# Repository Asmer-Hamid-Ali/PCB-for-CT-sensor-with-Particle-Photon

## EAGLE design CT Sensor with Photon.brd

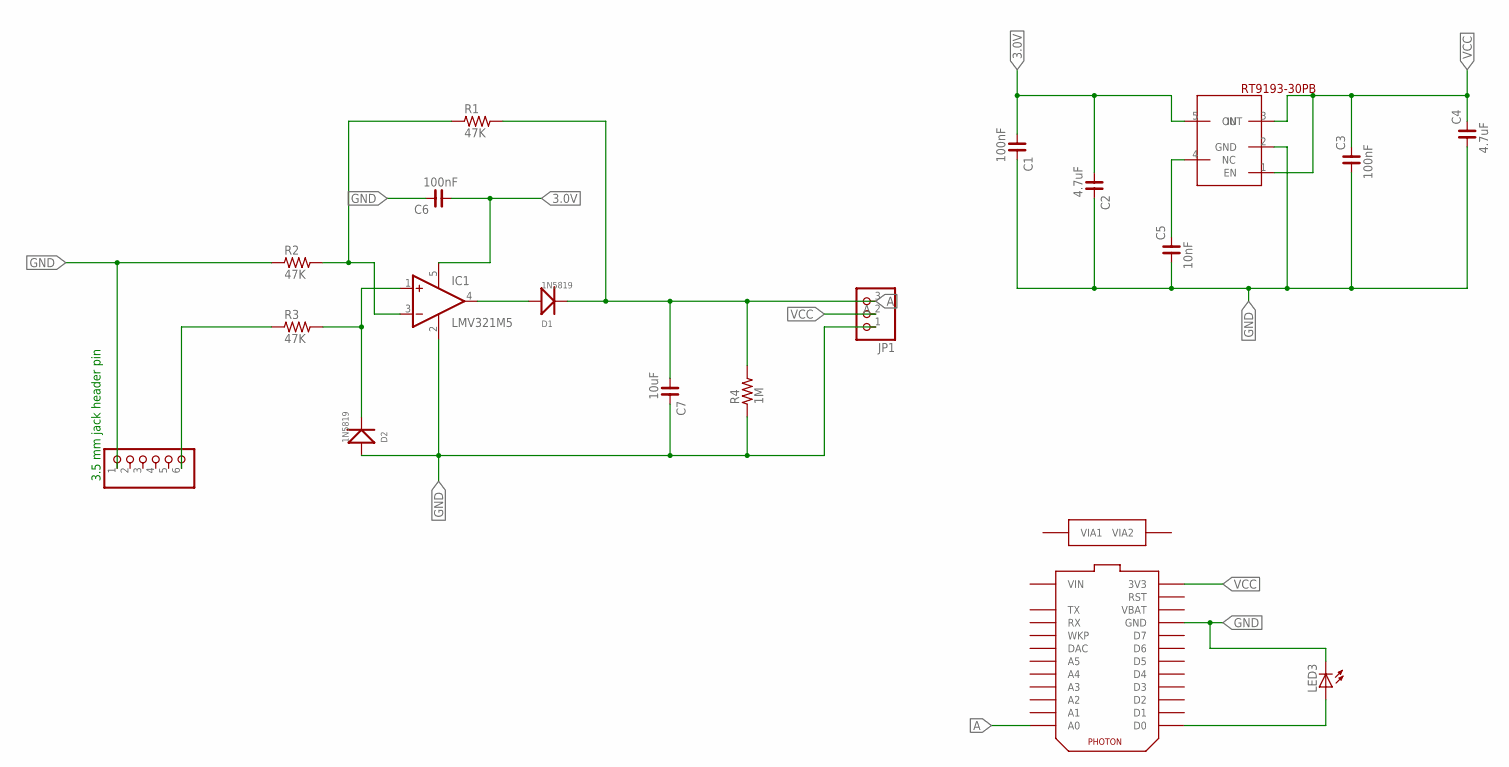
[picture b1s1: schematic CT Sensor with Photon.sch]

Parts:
C1, C3, C6: 100nF; C0201
C2, C4: 4.7uF; C0201
C5: 10nF; C0201
C7: 10uF; C0201
D1, D2: 1N5819; SOD-123
IC1: LMV321M5; SOT23-5
JP1: PINHD-1X3; 1X03
JP2: PINHD-1X6; 1X06
LED3: LED; SMARTLED-TTW
R1, R2, R3: 47K; R0201
R4: 1M; R0201
U$1: RT9193-30PB; SOP65P212X110-6N
U$2: TEMPLATE_PHOTON_RAW; PHOTON_RAW

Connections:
3.0V: C1.1, C2.1, C6.1, IC1.5 (V+), U$1.5 (OUT)
A: C7.1, D1.K, JP1.3, R1.2, R4.2, U$2.A0, U$2.A0. (A0), U$2.A0@1 (A0)
GND: C1.2, C2.2, C3.1, C4.1, C5.1, C6.2, C7.2, D2.A, IC1.2 (V-), JP1.1, JP2.1, LED3.C@1 (C), R2.1, R4.1, U$1.2 (GND), U$2.GND, U$2.GND1 (GND), U$2.GND. (GND), U$2.GND.@1 (GND), U$2.GND@1 (GND), U$2.GND@2 (GND)
unnamed: D2.K, IC1.1 (+IN), R3.2
unnamed: C5.2, U$1.4 (NC)
unnamed: IC1.3 (-IN), R1.1, R2.2
unnamed: D1.A, IC1.4 (OUT)
unnamed: LED3.A@1 (A), U$2.D0, U$2.D0. (D0), U$2.D0@1 (D0)
unnamed: JP2.6, R3.1
VCC: C3.2, C4.2, JP1.2, U$1.1 (EN), U$1.3 (IN), U$2.3V3, U$2.3V3. (3V3), U$2.3V31 (3V3)

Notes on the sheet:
3.5 mm jack header pin

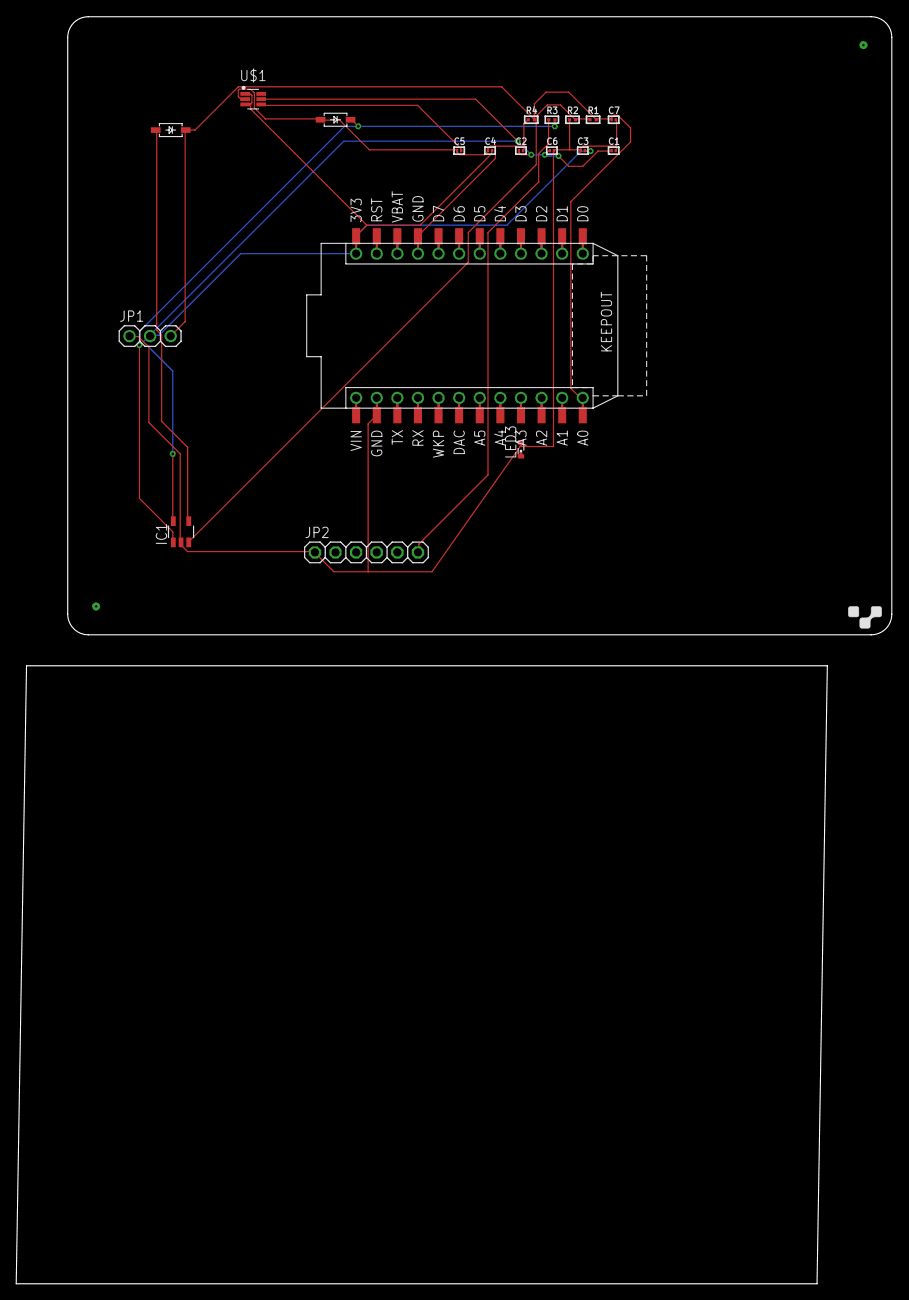
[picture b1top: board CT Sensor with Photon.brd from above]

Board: 2 copper layers, 101.6 x 76.2 mm, 19 parts (0 on the bottom side), 10 nets.

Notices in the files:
parts and their libraries:
rc-master-smd: Copyright (C) 2007, Bob Starr
